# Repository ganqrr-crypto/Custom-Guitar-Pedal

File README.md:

# Custom Guitar Pedal

This project is a fuzz guitar pedal made for half life by hack club and for fun..
it features a simple enclosure and a simple pcb and isn't too complex.

## Bill of Materials (BOM)

| Name | Purpose | Quantity | Price Euro | Total euro | Total $ | Links | Vendor |
| :--- | :--- | :---: | :---: | :---: | :---: | :--- | :--- |
| **2 M metal film 1%** | Resistor | 2 | €0.08 | €0.16 | $0.18 | https://www.musikding.de/2-M-metal-film-1 | Musikding |
| **390k metal film 1%** | Resistor | 1 | €0.08 | €0.08 | $0.09 | https://www.musikding.de/390k-metal-film-1 | Musikding |
| **100R metal film 1%** | Resistor | 2 | €0.08 | €0.16 | $0.18 | https://www.musikding.de/100R-metal-film-1 | Musikding |
| **BC549C** | Transistor | 4 | €0.06 | €0.24 | $0.27 | https://www.musikding.de/BC549C_1 | Musikding |
| **1N914** | Diode | 5 | €0.04 | €0.20 | $0.22 | https://www.musikding.de/1N914_1 | Musikding |
| **1N5817** | Schottky Diode | 1 | €0.10 | €0.10 | $0.11 | https://www.musikding.de/1N5817_1 | Musikding |
| **470k metal film 1%** | Resistor | 5 | €0.08 | €0.40 | $0.45 | https://www.musikding.de/470k-metal-film-1 | Musikding |
| **39k metal film 1%** | Resistor | 3 | €0.08 | €0.24 | $0.27 | https://www.musikding.de/39k-metal-film-1 | Musikding |
| **15k metal film 1%** | Resistor | 4 | €0.08 | €0.32 | $0.36 | https://www.musikding.de/15k-metal-film-1 | Musikding |
| **1k metal film 0,4W 1%** | Resistor | 1 | €0.08 | €0.08 | $0.09 | https://www.musikding.de/1k-metal-film-04W-1 | Musikding |
| **10k metal film 1%** | Resistor | 3 | €0.08 | €0.24 | $0.27 | https://www.musikding.de/10k-metal-film-1_1 | Musikding |
| **33k metal film 1%** | Resistor | 2 | €0.08 | €0.16 | $0.18 | https://www.musikding.de/33k-metal-film-1 | Musikding |
| **22k metal film 1%** | Resistor | 2 | €0.08 | €0.16 | $0.18 | https://www.musikding.de/22k-metal-film-1 | Musikding |
| **150R metal film 1%** | Resistor | 1 | €0.08 | €0.08 | $0.09 | https://www.musikding.de/150R-metal-film-1 | Musikding |
| **47k metal film 0,4W 1%** | Resistor | 2 | €0.08 | €0.16 | $0.18 | https://www.musikding.de/47k-metal-film-04W-1 | Musikding |
| **470uF/16V radial** | Capacitor | 2 | €0.16 | €0.32 | $0.36 | https://www.musikding.de/470uF-16V-radial_1 | Musikding |
| **Ceramic Disc 470 pF** | Capacitor | 5 | €0.06 | €0.30 | $0.34 | https://www.musikding.de/Ceramic-Disc-470-pF | Musikding |
| **Ceramic Disc 3,3 nF** | Capacitor | 1 | €0.06 | €0.06 | $0.07 | https://www.musikding.de/Ceramic-Disc-33-nF | Musikding |
| **PS 0,1uF 400V** | Capacitor | 4 | €0.15 | €0.60 | $0.67 | https://www.musikding.de/PS-01uF-400V_1 | Musikding |
| **1uF/350V radial** | Capacitor | 4 | €0.12 | €0.48 | $0.54 | https://www.musikding.de/1uF-350V-radial_1 | Musikding |
| **10uF/25V radial** | Capacitor | 2 | €0.08 | €0.16 | $0.18 | https://www.musikding.de/10uF-25V-radial_1 | Musikding |
| **Alpha Potentiometer 16mm 100k lin** | Potentiometer | 3 | €1.10 | €3.30 | $3.70 | https://www.musikding.de/Alpha-Potentiometer-16mm-100k-lin_1 | Musikding |
| **Toggleswitch SPDT** | Switch | 1 | €0.80 | €0.80 | $0.90 | https://www.musikding.de/Toggleswitch-SPDT | Musikding |
| **9V battery snap I-shape** | Battery Connector | 1 | €0.25 | €0.25 | $0.28 | https://www.musikding.de/9V-battery-snap-I-shape | Musikding |
| **3PDT footswitch** | Footswitch | 1 | €3.90 | €3.90 | $4.37 | https://www.musikding.de/3PDT-footswitch | Musikding |
| **DC power jack 2,1mm isolated** | Power Jack | 1 | €0.55 | €0.55 | $0.62 | https://www.musikding.de/DC-power-jack-21mm-isolated | Musikding |
| **6,3mm Stereo jack open** | Jack | 2 | €0.95 | €1.90 | $2.13 | https://www.musikding.de/63mm-Stereo-jack-open | Musikding |
| **PCB** | PCB | 5 | - | €1.21 | $1.35 | https://jlcpcb.com/ | JLCPCB |
| **SHIPPING** | Shipping | 1 | - | €5.90 | $6.61 | - | - |
| **TOTAL** | | **71** | | **€22.51** | **$25.21** | | |

here are some photos :

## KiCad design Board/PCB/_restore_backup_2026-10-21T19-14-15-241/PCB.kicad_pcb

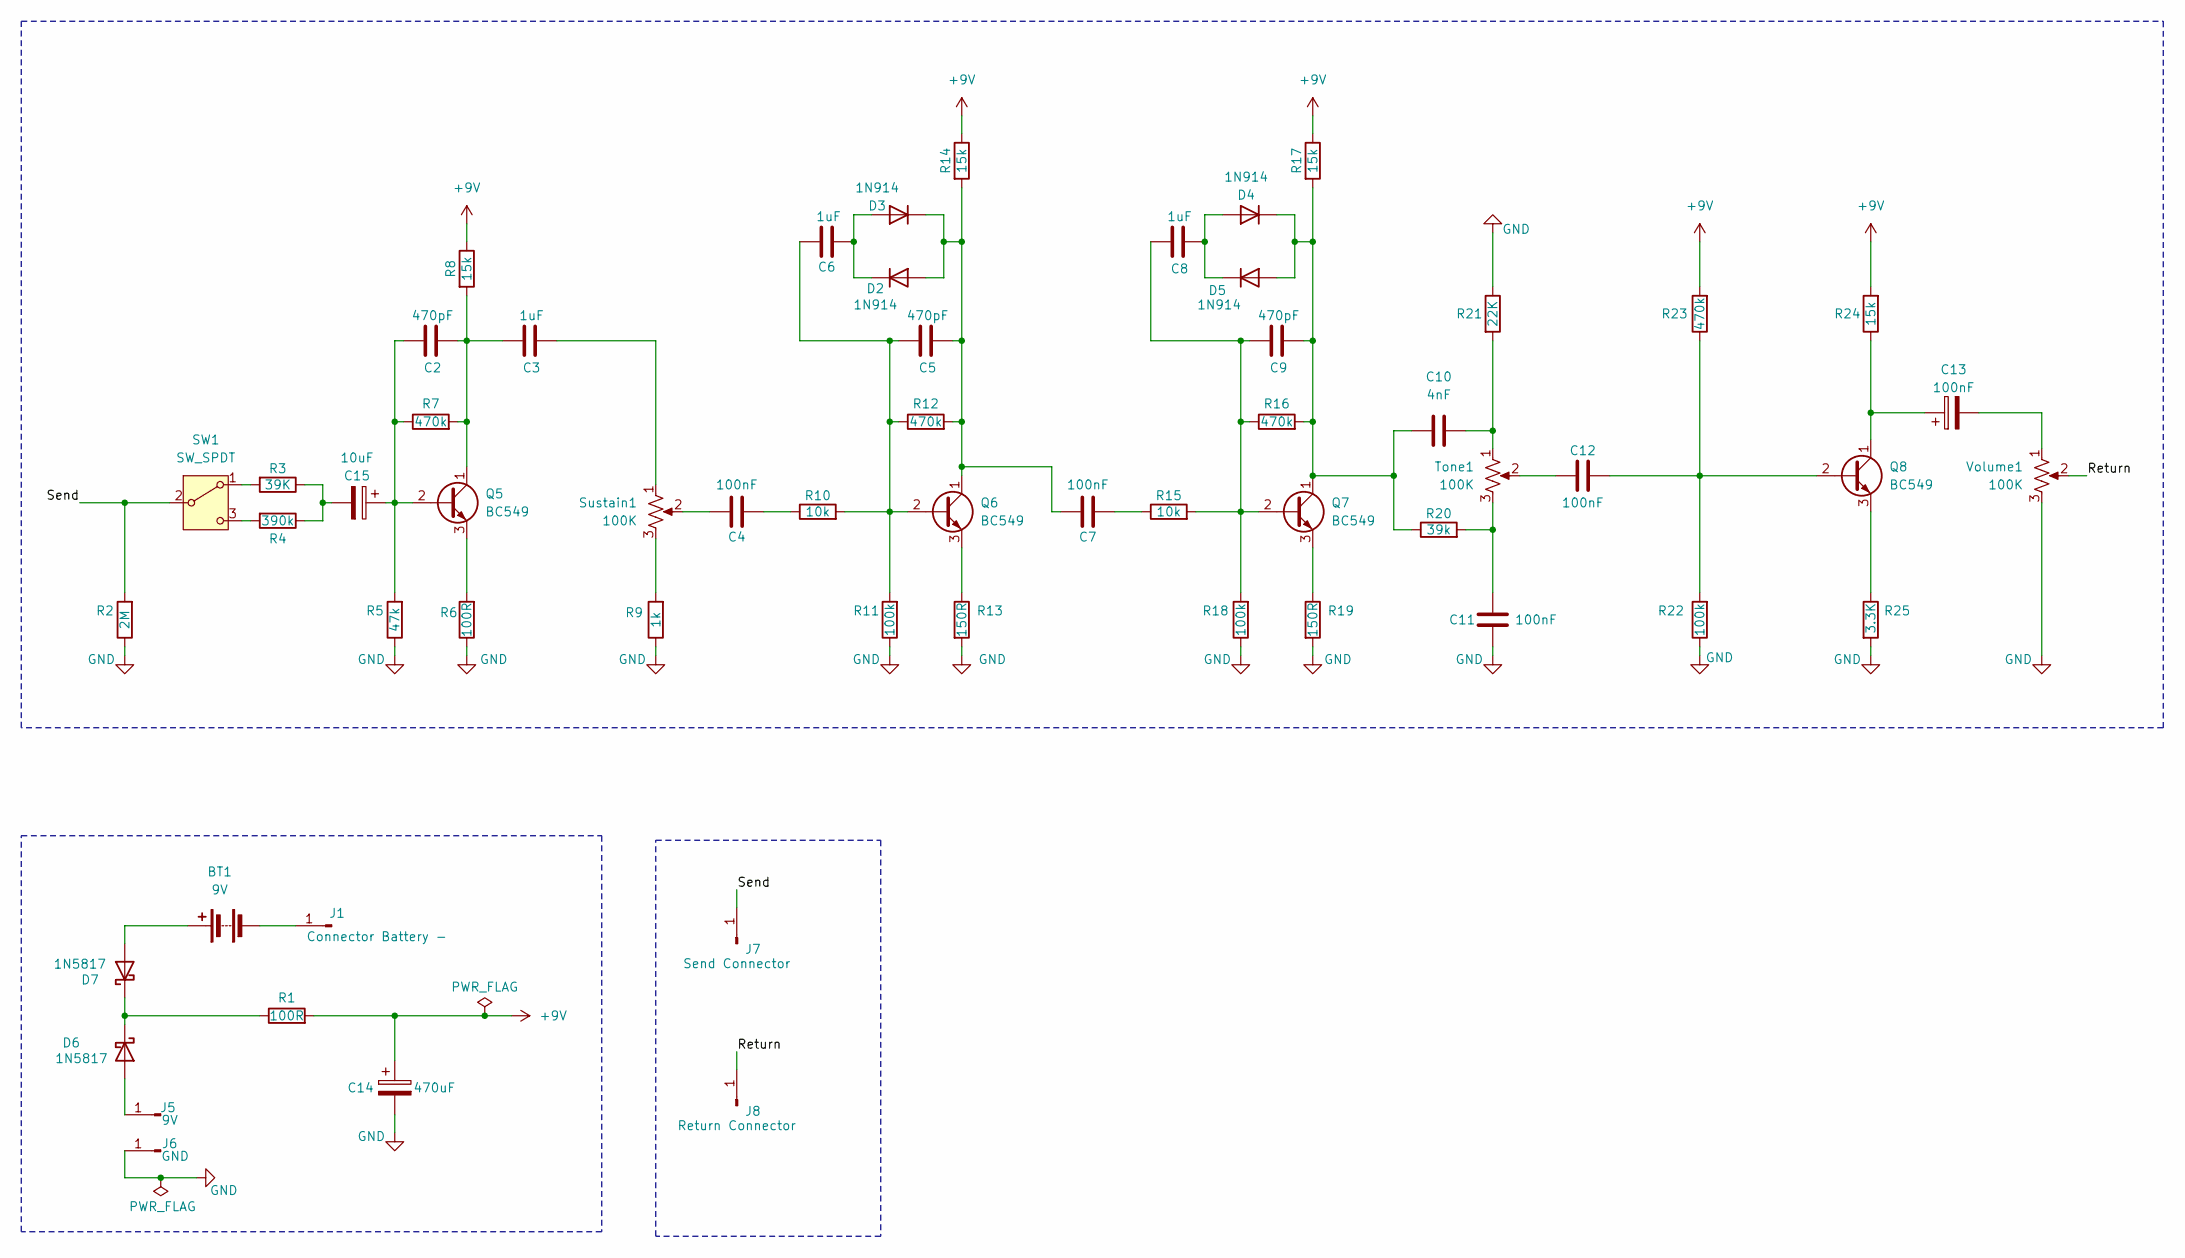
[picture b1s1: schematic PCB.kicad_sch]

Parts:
BT1: 9V; PinHeader_1x02_P2.54mm_Vertical
C2, C5, C9: 470pF; C_Disc_D5.0mm_W2.5mm_P2.50mm
C3, C6, C8: 1uF; CP_Radial_D6.3mm_P2.50mm
C4, C7, C11, C12, C13: 100nF; C_Rect_L13.0mm_W5.0mm_P10.00mm_FKS3_FKP3_MKS4
C10: 4nF; C_Disc_D5.0mm_W2.5mm_P5.00mm
C14: 470uF; C_Radial_D8.0mm_H11.5mm_P3.50mm
C15: 10uF; CP_Radial_D4.0mm_P1.50mm
D2, D3, D4, D5: 1N914; D_DO-35_SOD27_P7.62mm_Horizontal
D6, D7: 1N5817; D_DO-41_SOD81_P10.16mm_Horizontal
J1: Connector Battery -; TestPoint_THTPad_D2.0mm_Drill1.0mm
J5: 9V; TestPoint_THTPad_D2.0mm_Drill1.0mm
J6: GND; TestPoint_THTPad_D2.0mm_Drill1.0mm
J7: Send Connector; TestPoint_THTPad_D2.0mm_Drill1.0mm
J8: Return Connector; TestPoint_THTPad_D2.0mm_Drill1.0mm
Q5, Q6, Q7, Q8: BC549; TO-92_Inline
R1, R6: 100R; R_Axial_DIN0207_L6.3mm_D2.5mm_P7.62mm_Horizontal
R2: 2M; R_Axial_DIN0207_L6.3mm_D2.5mm_P7.62mm_Horizontal
R3: 39K; R_Axial_DIN0207_L6.3mm_D2.5mm_P7.62mm_Horizontal
R4: 390k; R_Axial_DIN0207_L6.3mm_D2.5mm_P7.62mm_Horizontal
R5: 47k; R_Axial_DIN0207_L6.3mm_D2.5mm_P7.62mm_Horizontal
R7, R12, R16, R23: 470k; R_Axial_DIN0207_L6.3mm_D2.5mm_P7.62mm_Horizontal
R8, R14, R17, R24: 15k; R_Axial_DIN0207_L6.3mm_D2.5mm_P7.62mm_Horizontal
R9: 1k; R_Axial_DIN0207_L6.3mm_D2.5mm_P7.62mm_Horizontal
R10, R15: 10k; R_Axial_DIN0207_L6.3mm_D2.5mm_P7.62mm_Horizontal
R11, R18, R22: 100k; R_Axial_DIN0207_L6.3mm_D2.5mm_P7.62mm_Horizontal
R13, R19: 150R; R_Axial_DIN0207_L6.3mm_D2.5mm_P7.62mm_Horizontal
R20: 39k; R_Axial_DIN0207_L6.3mm_D2.5mm_P7.62mm_Horizontal
R21: 22K; R_Axial_DIN0207_L6.3mm_D2.5mm_P7.62mm_Horizontal
R25: 3.3K; R_Axial_DIN0207_L6.3mm_D2.5mm_P7.62mm_Horizontal
SW1: SW_SPDT; PinHeader_1x03_P2.54mm_Vertical
Sustain1: 100K; PinHeader_1x03_P2.54mm_Vertical
Tone1: 100K; PinHeader_1x03_P2.54mm_Vertical
Volume1: 100K; PinHeader_1x03_P2.54mm_Vertical

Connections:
+9V: C14.1, R1.2, R8.1, R14.1, R17.1, R23.2, R24.2
/Return: J8.1 (Pin_1_1), Volume1.2
/Send: J7.1, R2.2, SW1.2 (B); also elsewhere on the board
GND: C11.2, C14.2, J6.1, R2.1, R5.1, R6.1, R9.1, R11.1, R13.2, R18.1, R19.2, R21.1, R22.1, R25.2, Volume1.3; also elsewhere on the board
unnamed: BT1.1 (+), D7.2 (A)
unnamed 5: BT1.2 (-), J1.1; also elsewhere on the board
unnamed: C3.2, Sustain1.1
unnamed: C4.1, Sustain1.2
unnamed: C4.2, R10.1
unnamed: C7.2, R15.1
unnamed: C10.2, R21.2, Tone1.1
unnamed: C11.1, R20.2, Tone1.3
unnamed: C12.2, Tone1.2
unnamed: C13.2, Volume1.1
unnamed: C15.2, R3.1, R4.1
unnamed: C5.2, C7.1, D2.2 (A), D3.1 (K), Q6.1 (C), R12.2, R14.2
unnamed: C6.2, D2.1 (K), D3.2 (A)
unnamed: C8.2, D4.2 (A), D5.1 (K)
unnamed: C9.2, C10.1, D4.1 (K), D5.2 (A), Q7.1 (C), R16.2, R17.2, R20.1
unnamed 19: D6.2 (A), J5.1; also elsewhere on the board
unnamed: D6.1 (K), D7.1 (K), R1.1
unnamed: C2.1, C15.1, Q5.2 (B), R5.2, R7.1
unnamed: C2.2, C3.1, Q5.1 (C), R7.2, R8.2
unnamed: Q5.3 (E), R6.2
unnamed: C5.1, C6.1, Q6.2 (B), R10.2, R11.2, R12.1
unnamed: Q6.3 (E), R13.1
unnamed: C8.1, C9.1, Q7.2 (B), R15.2, R16.1, R18.2
unnamed: Q7.3 (E), R19.1
unnamed: C12.1, Q8.2 (B), R22.2, R23.1
unnamed: C13.1, Q8.1 (C), R24.1
unnamed: Q8.3 (E), R25.1
unnamed: R9.2, Sustain1.3
unnamed: R3.2, SW1.1 (A)
unnamed: R4.2, SW1.3 (C)

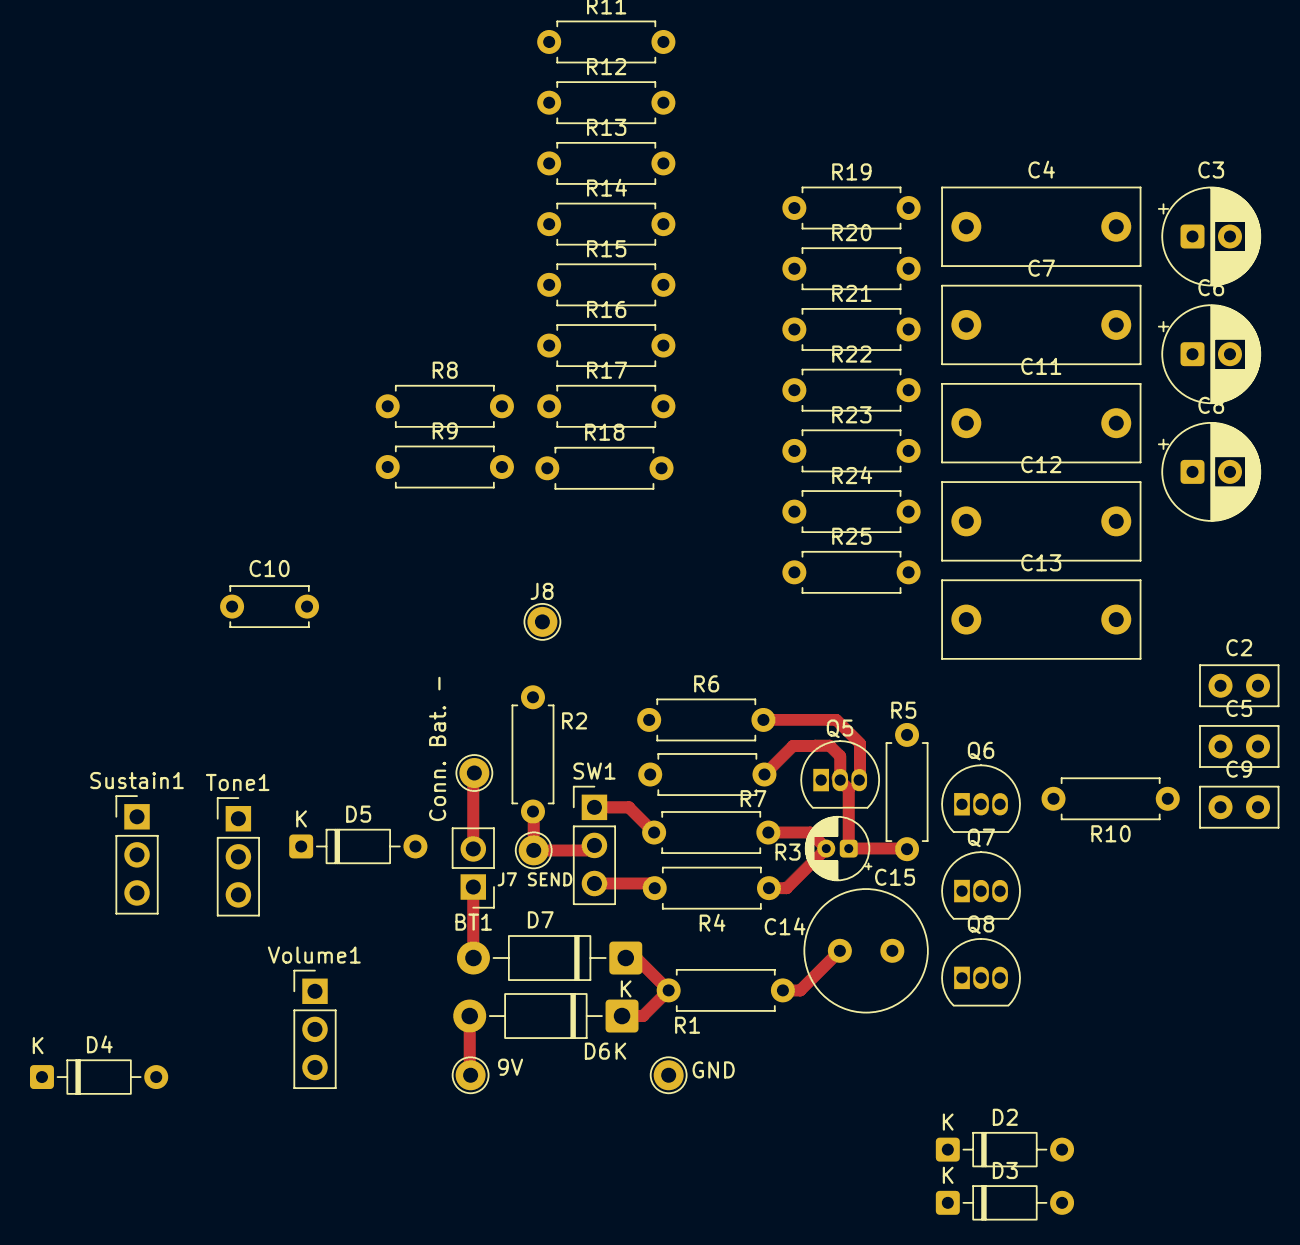
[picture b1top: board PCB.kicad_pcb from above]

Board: 2 copper layers, 59 parts (0 on the bottom side), 34 nets.

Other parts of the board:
9V: 9V; TestPoint_THTPad_D2.0mm_Drill1.0mm
Conn. Bat. -: Connector Battery -; TestPoint_THTPad_D2.0mm_Drill1.0mm
GND: GND; TestPoint_THTPad_D2.0mm_Drill1.0mm
J7 SEND: Send Connector; TestPoint_THTPad_D2.0mm_Drill1.0mm

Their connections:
/Send: J7 SEND.1 (Pin_1_1); also elsewhere on the board
GND: GND.1 (Pin_1_1); also elsewhere on the board
unnamed 5: Conn. Bat. -.1 (Pin_1_1); also elsewhere on the board
unnamed 19: 9V.1 (Pin_1_1); also elsewhere on the board
